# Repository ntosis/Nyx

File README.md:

# Nyx
Nyx Project is a FOC algorith for PMSM Motors based on ARM STM32F446RE, DRV8304 and Simulink. 

The Project NYX is under development and the application software has been developed with Simulink. 
The PCB is not ready and based on DRV8304 fromm Texas Instruments. 
The first tries has been made on EVAL Board from Texas Instruments 'boostxl-drv8304h'

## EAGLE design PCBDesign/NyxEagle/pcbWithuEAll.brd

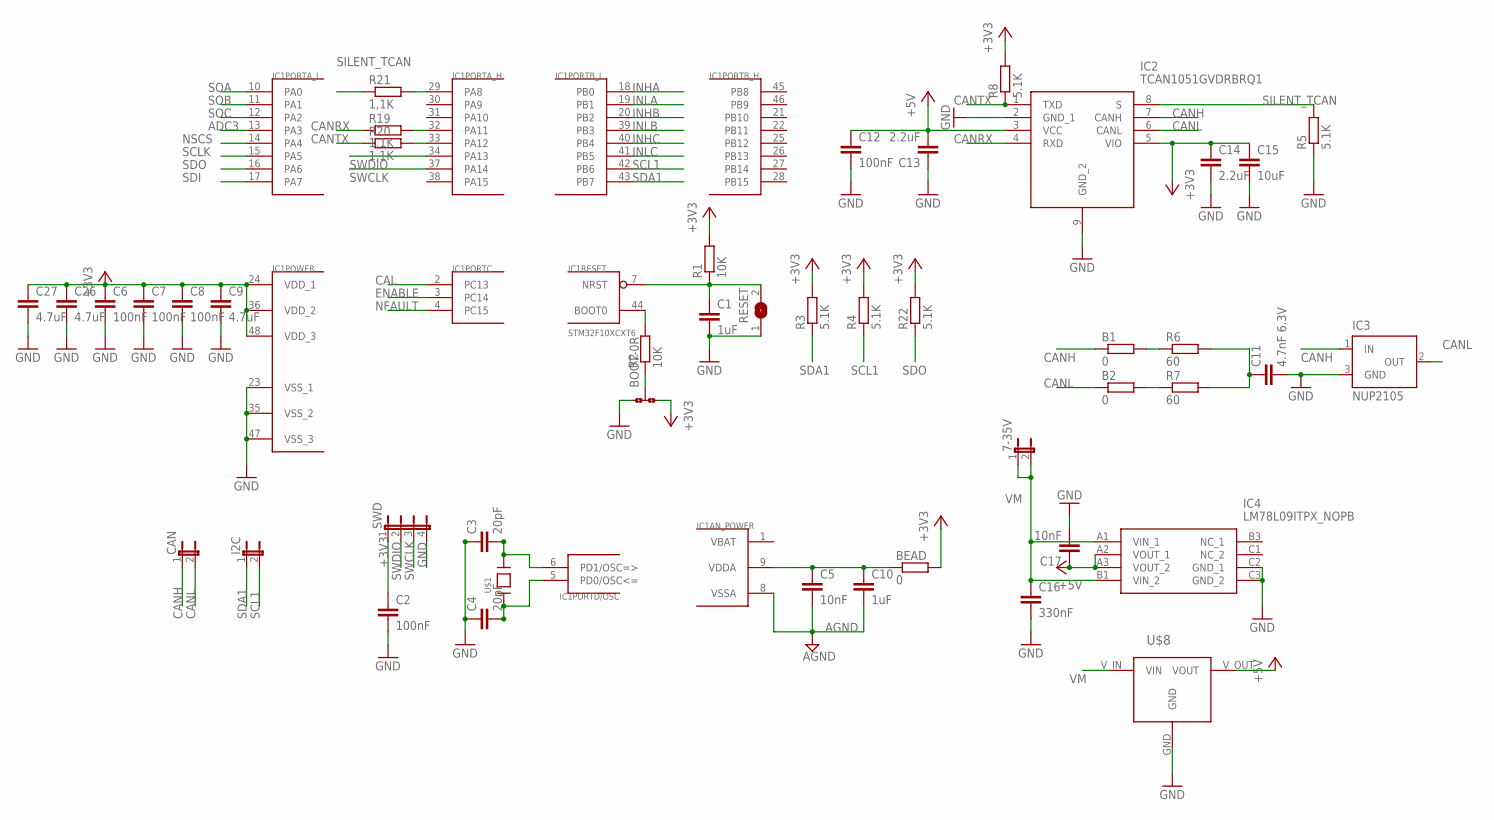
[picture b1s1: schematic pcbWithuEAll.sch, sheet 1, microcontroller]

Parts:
7-35V: JP1E; JP1
B1, B2: 0; R0805
BEAD: 0; R0805
BOOT: 0R-JUMPB; B0R-JMP
C1: 1uF; C0603
C2, C6, C7, C8, C12: 100nF; C0603
C3, C4: 20pF; C0603
C5, C17: 10nF; C0603
C9, C26, C27: 4.7uF; C0603
C10: 1uF; C0805K
C11: 4.7nF 6.3V; C0603
C13, C14: 2.2uF; C0603
C15: 10uF; C0603
C16: 330nF; C0603
CAN: JP1E; JP1
I2C: JP1E; JP1
IC1: STM32F10XCXT6; TQFP48
IC2: TCAN1051GVDRBRQ1; DRB-8
IC3: NUP2105; SOT23
IC4: LM78L09ITPX_NOPB; BGA8C50P3X3_131X131X58
R1, R2: 10K; R0603
R3, R4, R8, R22: 5.1K; R0603
R5: 5.1K; R0402
R6, R7: 60; R0603
R19, R20, R21: 1,1K; R0603
RESET: SJ
SWD: JP4E; JP4
U$1: QUARZ8MHZ; SMD5*3.2MM
U$8: MCP1799T-3302H; SOT23

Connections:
+3V3: BEAD.2, BOOT.3, C2.1, C6.1, C7.1, C8.1, C9.1, C14.1, C15.1, C26.1, C27.1, IC1.24 (VDD_1), IC1.36 (VDD_2), IC1.48 (VDD_3), IC2.5 (VIO), R1.2, R3.2, R4.2, R8.2, R22.2, SWD.1; also elsewhere on the board
+5V: C12.1, C13.2, C17.1, IC2.3 (VCC), IC4.A2 (VOUT_1), IC4.A3 (VOUT_2), U$8.V_OUT (VOUT)
ADC3: IC1.13 (PA3)
AGND: C5.2, C10.2, IC1.8 (VSSA); also elsewhere on the board
CAL: IC1.2 (PC13); also elsewhere on the board
CANH: B1.1, CAN.1, IC2.7 (CANH), IC3.1 (IN)
CANL: B2.1, CAN.2, IC2.6 (CANL), IC3.2 (OUT)
CANRX: IC2.4 (RXD), R19.1
CANTX: IC2.1 (TXD), R8.1, R20.1
ENABLE: IC1.3 (PC14); also elsewhere on the board
GND: BOOT.1, C1.2, C2.2, C3.1, C4.1, C6.2, C7.2, C8.2, C9.2, C11.2, C12.2, C13.1, C14.2, C15.2, C16.2, C17.2, C26.2, C27.2, IC1.23 (VSS_1), IC1.35 (VSS_2), IC1.47 (VSS_3), IC2.2 (GND_1), IC2.9 (GND_2), IC3.3 (GND), IC4.C2 (GND_1), IC4.C3 (GND_2), R5.1, RESET.1, SWD.4, U$8.GND; also elsewhere on the board
INHA: IC1.18 (PB0); also elsewhere on the board
INHB: IC1.20 (PB2); also elsewhere on the board
INHC: IC1.40 (PB4); also elsewhere on the board
INLA: IC1.19 (PB1); also elsewhere on the board
INLB: IC1.39 (PB3); also elsewhere on the board
INLC: IC1.41 (PB5); also elsewhere on the board
unnamed: C1.1, IC1.7 (NRST), R1.1, RESET.2
unnamed: C3.2, IC1.6 (PD1/OSC=>), U$1.P$2
unnamed: C4.2, IC1.5 (PD0/OSC<=), U$1.P$1
unnamed: IC1.44 (BOOT0), R2.2
unnamed: BEAD.1, C5.1, C10.1, IC1.9 (VDDA)
unnamed: BOOT.2, R2.1
unnamed: C11.1, R6.2, R7.2
unnamed: B1.2, R6.1
unnamed: B2.2, R7.1
unnamed: IC1.32 (PA11), R19.2
unnamed: IC1.33 (PA12), R20.2
unnamed: IC1.29 (PA8), R21.2
NFAULT: IC1.4 (PC15); also elsewhere on the board
NSCS: IC1.14 (PA4); also elsewhere on the board
SCL1: I2C.2, IC1.42 (PB6), R4.1
SCLK: IC1.15 (PA5); also elsewhere on the board
SDA1: I2C.1, IC1.43 (PB7), R3.1
SDI: IC1.17 (PA7); also elsewhere on the board
SDO: IC1.16 (PA6), R22.1; also elsewhere on the board
SILENT_TCAN: IC2.8 (S), R5.2, R21.1
SOA: IC1.10 (PA0); also elsewhere on the board
SOB: IC1.11 (PA1); also elsewhere on the board
SOC: IC1.12 (PA2); also elsewhere on the board
SWCLK: IC1.37 (PA14), SWD.3
SWDIO: IC1.34 (PA13), SWD.2
VBAT: IC1.1 (VBAT)
VM: 7-35V.1, 7-35V.2, C16.1, IC4.A1 (VIN_1), IC4.B1 (VIN_2), U$8.V_IN (VIN); also elsewhere on the board

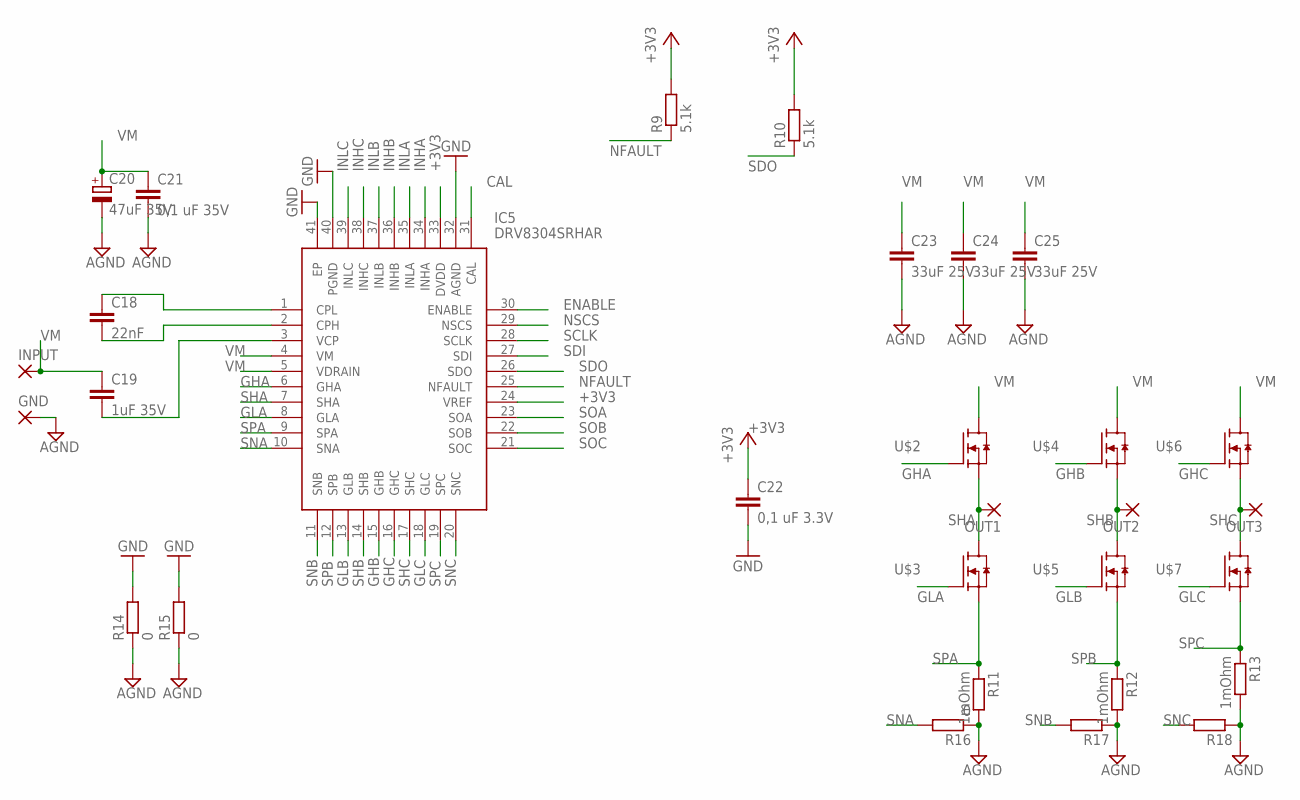
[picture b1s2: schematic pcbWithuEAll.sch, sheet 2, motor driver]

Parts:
C18: 22nF; C0805K
C19: 1uF 35V; C0805K
C20: 47uF 35V; E7,5-16
C21: 0,1 uF 35V; C0805K
C22: 0,1 uF 3.3V; C0805K
C23, C24, C25: 33uF 25V; C1206K
GND: 3,17/1,3
IC5: DRV8304SRHAR; QFN50P600X600X100-41N
INPUT: 3,17/1,3
OUT1, OUT2, OUT3: SMD2; SMD1,27-2,54
R9, R10: 5.1k; R0603
R11, R12, R13: 1mOhm; 1216
R14, R15: 0; R0805W
R16: 0; R0201
R17, R18: R-EU_R0201; R0201
U$2, U$3, U$4, U$5, U$6, U$7: SIRA80DP-T1-RE3-CLASSIC; SI7852ADPT1GE3

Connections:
+3V3: C22.1, IC5.24 (VREF), IC5.33 (DVDD), R9.2, R10.2; also elsewhere on the board
AGND: C20.-, C21.2, C23.2, C24.2, C25.2, GND.1, R11.P$2 (2), R11.P$4 (2), R12.P$2 (2), R12.P$4 (2), R13.P$2 (2), R13.P$4 (2), R14.1, R15.1, R16.1, R17.1, R18.1; also elsewhere on the board
CAL: IC5.31 (CAL); also elsewhere on the board
ENABLE: IC5.30 (ENABLE); also elsewhere on the board
GHA: IC5.6 (GHA), U$2.4 (G)
GHB: IC5.15 (GHB), U$4.4 (G)
GHC: IC5.16 (GHC), U$6.4 (G)
GLA: IC5.8 (GLA), U$3.4 (G)
GLB: IC5.13 (GLB), U$5.4 (G)
GLC: IC5.18 (GLC), U$7.4 (G)
GND: C22.2, IC5.32 (AGND), IC5.40 (PGND), IC5.41 (EP), R14.2, R15.2; also elsewhere on the board
INHA: IC5.34 (INHA); also elsewhere on the board
INHB: IC5.36 (INHB); also elsewhere on the board
INHC: IC5.38 (INHC); also elsewhere on the board
INLA: IC5.35 (INLA); also elsewhere on the board
INLB: IC5.37 (INLB); also elsewhere on the board
INLC: IC5.39 (INLC); also elsewhere on the board
unnamed: C18.1, IC5.1 (CPL)
unnamed: C18.2, IC5.2 (CPH)
unnamed: C19.2, IC5.3 (VCP)
NFAULT: IC5.25 (NFAULT), R9.1; also elsewhere on the board
NSCS: IC5.29 (NSCS); also elsewhere on the board
SCLK: IC5.28 (SCLK); also elsewhere on the board
SDI: IC5.27 (SDI); also elsewhere on the board
SDO: IC5.26 (SDO), R10.1; also elsewhere on the board
SHA: IC5.7 (SHA), OUT1.1, U$2.1 (S), U$2.2 (S), U$2.3 (S), U$3.5 (D), U$3.6 (D), U$3.7 (D), U$3.8 (D), U$3.9 (D), U$3.10 (D), U$3.11 (D)
SHB: IC5.14 (SHB), OUT2.1, U$4.1 (S), U$4.2 (S), U$4.3 (S), U$5.5 (D), U$5.6 (D), U$5.7 (D), U$5.8 (D), U$5.9 (D), U$5.10 (D), U$5.11 (D)
SHC: IC5.17 (SHC), OUT3.1, U$6.1 (S), U$6.2 (S), U$6.3 (S), U$7.5 (D), U$7.6 (D), U$7.7 (D), U$7.8 (D), U$7.9 (D), U$7.10 (D), U$7.11 (D)
SNA: IC5.10 (SNA), R16.2
SNB: IC5.11 (SNB), R17.2
SNC: IC5.20 (SNC), R18.2
SOA: IC5.23 (SOA); also elsewhere on the board
SOB: IC5.22 (SOB); also elsewhere on the board
SOC: IC5.21 (SOC); also elsewhere on the board
SPA: IC5.9 (SPA), R11.P$1 (1), R11.P$3 (1), U$3.1 (S), U$3.2 (S), U$3.3 (S)
SPB: IC5.12 (SPB), R12.P$1 (1), R12.P$3 (1), U$5.1 (S), U$5.2 (S), U$5.3 (S)
SPC: IC5.19 (SPC), R13.P$1 (1), R13.P$3 (1), U$7.1 (S), U$7.2 (S), U$7.3 (S)
VM: C19.1, C20.+, C21.1, C23.1, C24.1, C25.1, IC5.4 (VM), IC5.5 (VDRAIN), INPUT.1, U$2.5 (D), U$2.6 (D), U$2.7 (D), U$2.8 (D), U$2.9 (D), U$2.10 (D), U$2.11 (D), U$4.5 (D), U$4.6 (D), U$4.7 (D), U$4.8 (D), U$4.9 (D), U$4.10 (D), U$4.11 (D), U$6.5 (D), U$6.6 (D), U$6.7 (D), U$6.8 (D), U$6.9 (D), U$6.10 (D), U$6.11 (D); also elsewhere on the board

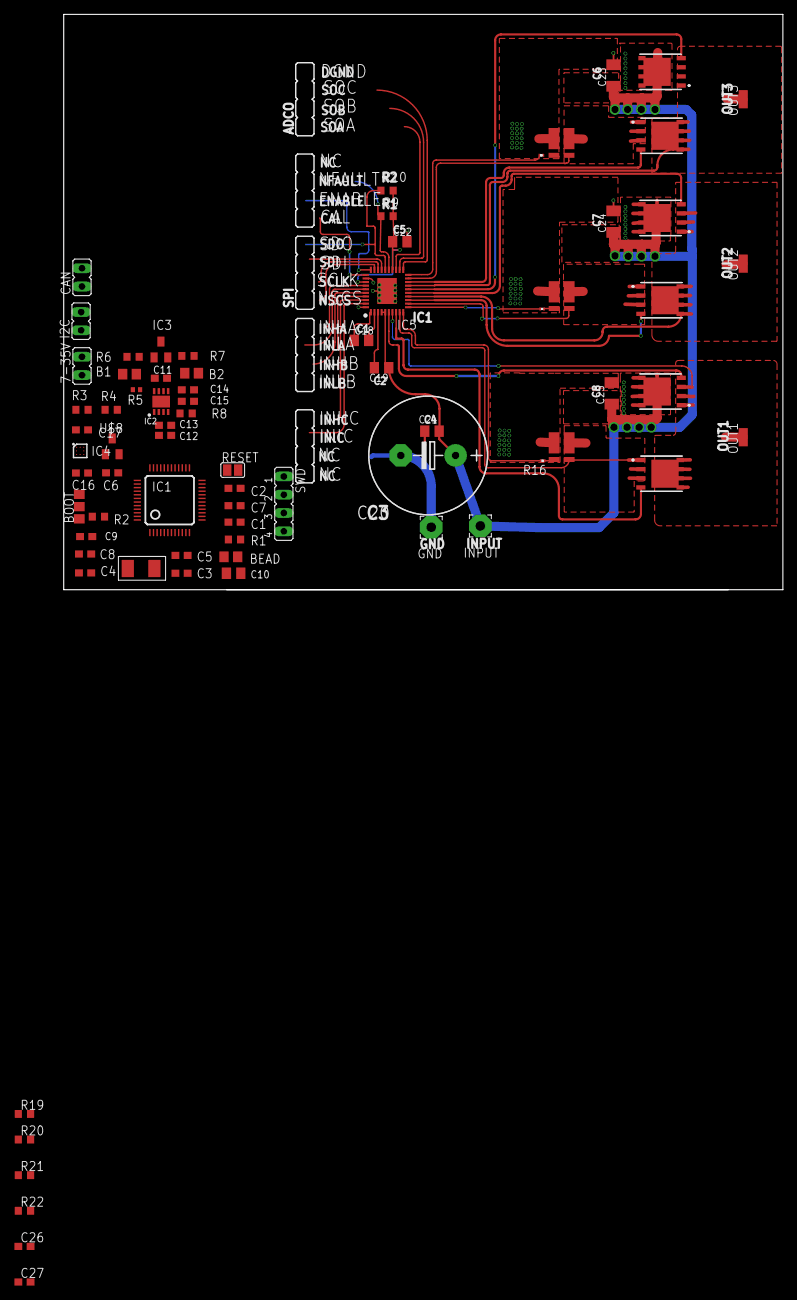
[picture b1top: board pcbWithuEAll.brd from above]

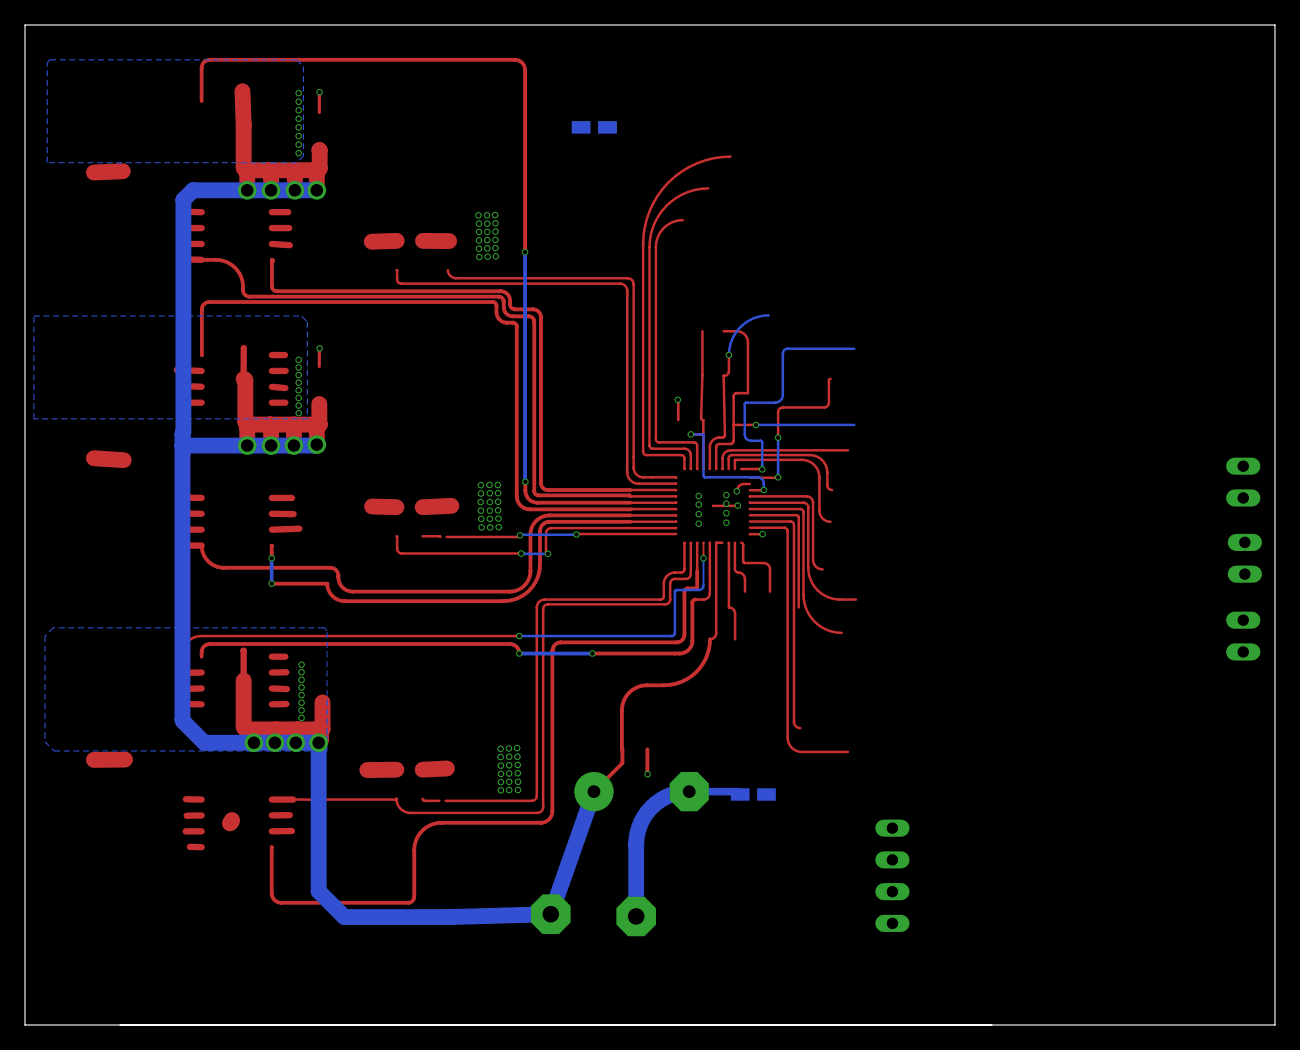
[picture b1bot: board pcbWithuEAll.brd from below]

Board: 2 copper layers, 100.0 x 80.0 mm, 76 parts (2 on the bottom side), 60 nets.

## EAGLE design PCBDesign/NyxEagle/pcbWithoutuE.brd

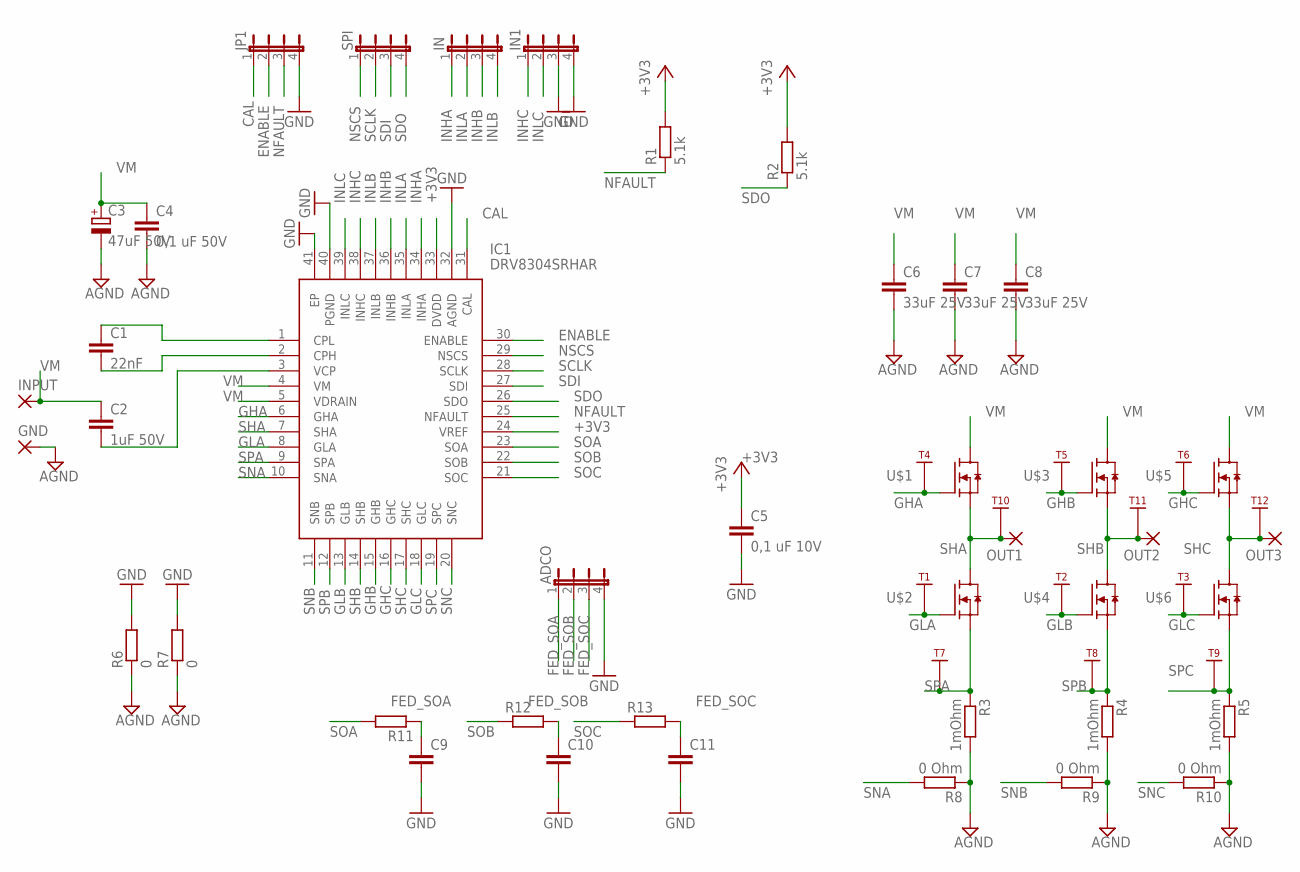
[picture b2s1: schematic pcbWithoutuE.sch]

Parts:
ADCO: JP4E; JP4
C1: 22nF; C0805K
C2: 1uF 50V; C0805K
C3: 47uF 50V; E7,5-16
C4: 0,1 uF 50V; C0805K
C5: 0,1 uF 10V; C0805K
C6, C7, C8: 33uF 25V; C1206K
C9, C10, C11: C-EUC0805; C0805
GND: 3,17/1,3
IC1: DRV8304SRHAR; QFN50P600X600X100-41N
IN, IN1: JP4E; JP4
INPUT: 3,17/1,3
JP1: JP4E; JP4
OUT1, OUT2, OUT3: SMD2; SMD1,27-2,54
R1, R2: 5.1k; R0805
R3, R4, R5: 1mOhm; 1216
R6, R7: 0; R0805W
R8, R9, R10: 0 Ohm; R0603
R11, R12, R13: R-EU_R0805; R0805
SPI: JP4E; JP4
T1, T2, T3, T4, T5, T6, T7, T8, T9, T10, T11, T12: TEST_POINT1593; TURRET_TERMINAL_1593
U$1, U$2, U$3, U$4, U$5, U$6: SIRA80DP-T1-RE3-CLASSIC; SI7852ADPT1GE3

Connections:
+3V3: C5.1, IC1.24 (VREF), IC1.33 (DVDD), R1.2, R2.2
AGND: C3.-, C4.2, C6.2, C7.2, C8.2, GND.1, R3.P$2 (2), R3.P$4 (2), R4.P$2 (2), R4.P$4 (2), R5.P$2 (2), R5.P$4 (2), R6.1, R7.1, R8.1, R9.1, R10.1
CAL: IC1.31 (CAL), JP1.1
ENABLE: IC1.30 (ENABLE), JP1.2
FED_SOA: ADCO.1, C9.1, R11.1
FED_SOB: ADCO.2, C10.1, R12.2
FED_SOC: ADCO.3, C11.1, R13.2
GHA: IC1.6 (GHA), T4.1, U$1.4 (G)
GHB: IC1.15 (GHB), T5.1, U$3.4 (G)
GHC: IC1.16 (GHC), T6.1, U$5.4 (G)
GLA: IC1.8 (GLA), T1.1, U$2.4 (G)
GLB: IC1.13 (GLB), T2.1, U$4.4 (G)
GLC: IC1.18 (GLC), T3.1, U$6.4 (G)
GND: ADCO.4, C5.2, C9.2, C10.2, C11.2, IC1.32 (AGND), IC1.40 (PGND), IC1.41 (EP), IN1.3, IN1.4, JP1.4, R6.2, R7.2
INHA: IC1.34 (INHA), IN.1
INHB: IC1.36 (INHB), IN.3
INHC: IC1.38 (INHC), IN1.1
INLA: IC1.35 (INLA), IN.2
INLB: IC1.37 (INLB), IN.4
INLC: IC1.39 (INLC), IN1.2
unnamed: C1.1, IC1.1 (CPL)
unnamed: C1.2, IC1.2 (CPH)
unnamed: C2.2, IC1.3 (VCP)
NFAULT: IC1.25 (NFAULT), JP1.3, R1.1
NSCS: IC1.29 (NSCS), SPI.1
SCLK: IC1.28 (SCLK), SPI.2
SDI: IC1.27 (SDI), SPI.3
SDO: IC1.26 (SDO), R2.1, SPI.4
SHA: IC1.7 (SHA), OUT1.1, T10.1, U$1.1 (S), U$1.2 (S), U$1.3 (S), U$2.5 (D), U$2.6 (D), U$2.7 (D), U$2.8 (D), U$2.9 (D), U$2.10 (D), U$2.11 (D)
SHB: IC1.14 (SHB), OUT2.1, T11.1, U$3.1 (S), U$3.2 (S), U$3.3 (S), U$4.5 (D), U$4.6 (D), U$4.7 (D), U$4.8 (D), U$4.9 (D), U$4.10 (D), U$4.11 (D)
SHC: IC1.17 (SHC), OUT3.1, T12.1, U$5.1 (S), U$5.2 (S), U$5.3 (S), U$6.5 (D), U$6.6 (D), U$6.7 (D), U$6.8 (D), U$6.9 (D), U$6.10 (D), U$6.11 (D)
SNA: IC1.10 (SNA), R8.2
SNB: IC1.11 (SNB), R9.2
SNC: IC1.20 (SNC), R10.2
SOA: IC1.23 (SOA), R11.2
SOB: IC1.22 (SOB), R12.1
SOC: IC1.21 (SOC), R13.1
SPA: IC1.9 (SPA), R3.P$1 (1), R3.P$3 (1), T7.1, U$2.1 (S), U$2.2 (S), U$2.3 (S)
SPB: IC1.12 (SPB), R4.P$1 (1), R4.P$3 (1), T8.1, U$4.1 (S), U$4.2 (S), U$4.3 (S)
SPC: IC1.19 (SPC), R5.P$1 (1), R5.P$3 (1), T9.1, U$6.1 (S), U$6.2 (S), U$6.3 (S)
VM: C2.1, C3.+, C4.1, C6.1, C7.1, C8.1, IC1.4 (VM), IC1.5 (VDRAIN), INPUT.1, U$1.5 (D), U$1.6 (D), U$1.7 (D), U$1.8 (D), U$1.9 (D), U$1.10 (D), U$1.11 (D), U$3.5 (D), U$3.6 (D), U$3.7 (D), U$3.8 (D), U$3.9 (D), U$3.10 (D), U$3.11 (D), U$5.5 (D), U$5.6 (D), U$5.7 (D), U$5.8 (D), U$5.9 (D), U$5.10 (D), U$5.11 (D)

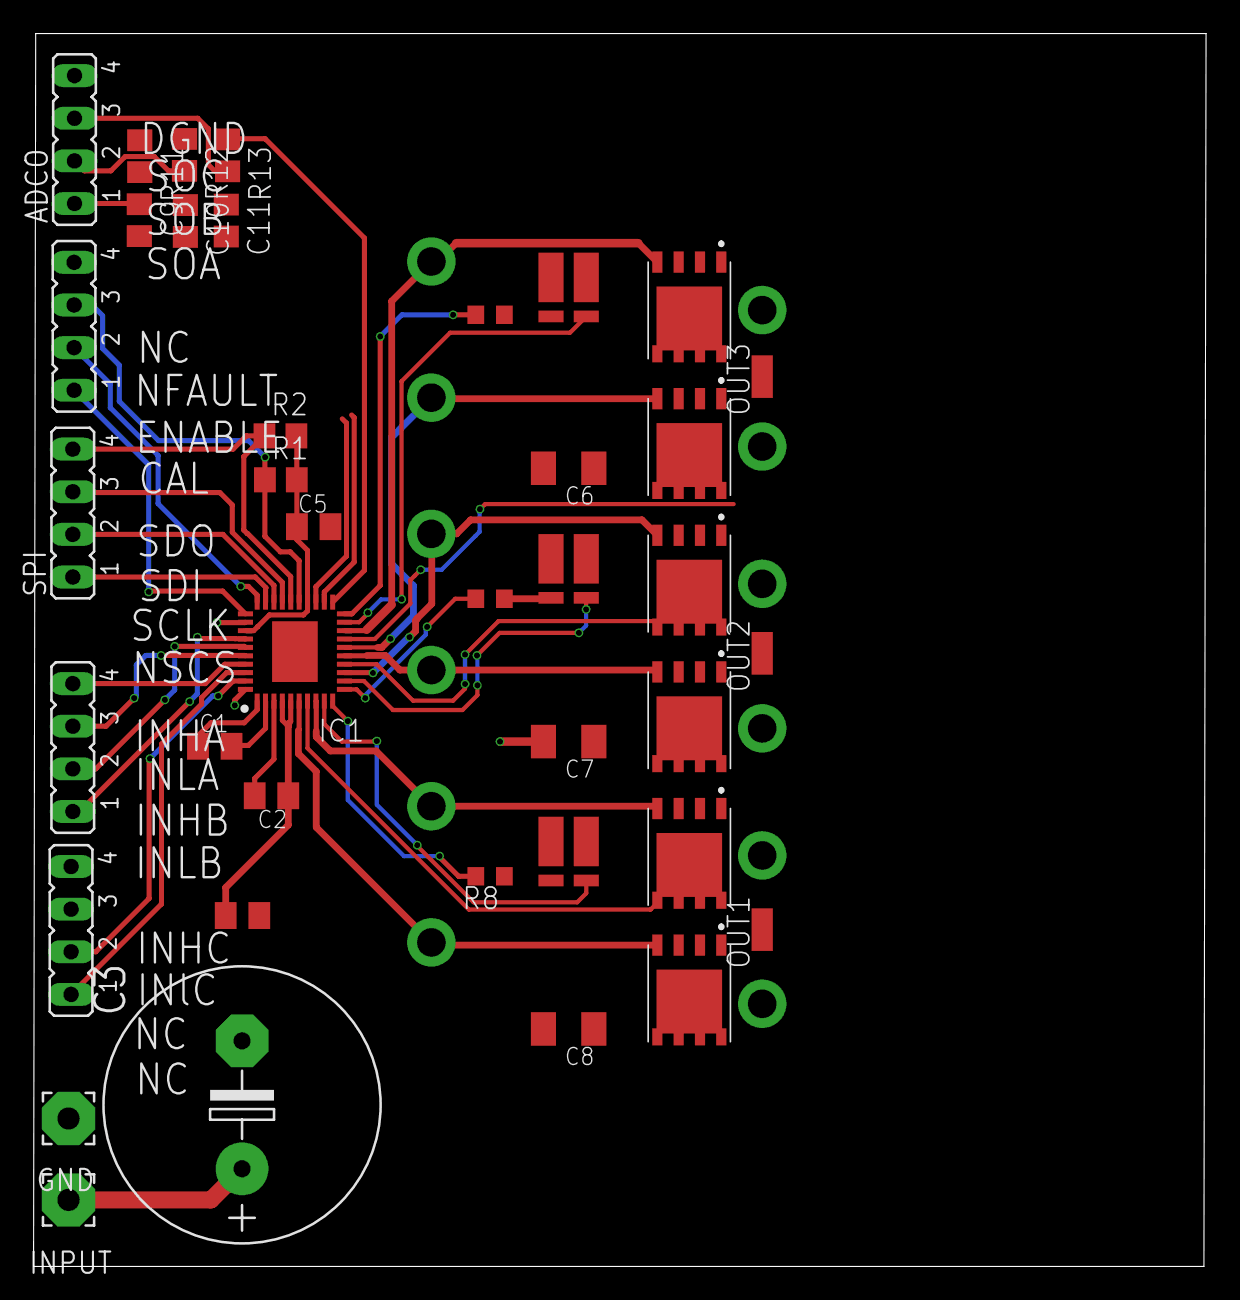
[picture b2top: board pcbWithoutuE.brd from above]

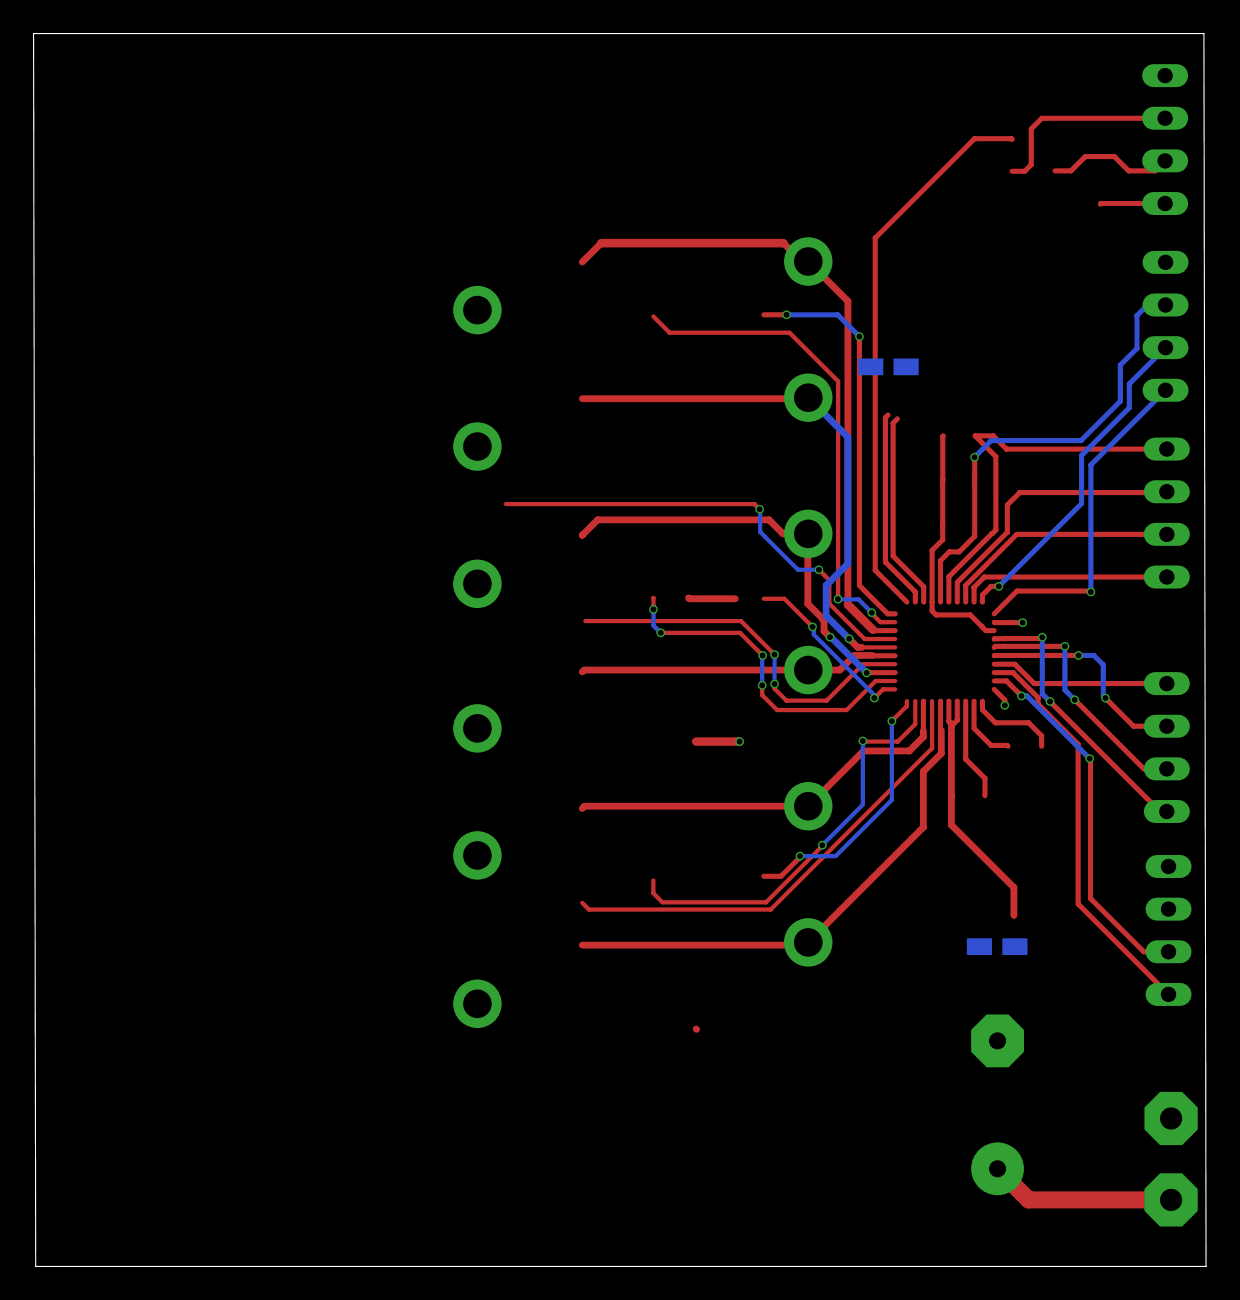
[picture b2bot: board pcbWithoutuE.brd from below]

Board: 2 copper layers, 69.9 x 73.4 mm, 53 parts (2 on the bottom side), 41 nets.

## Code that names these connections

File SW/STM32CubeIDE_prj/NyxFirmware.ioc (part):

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Mcu.Name=STM32F103C(8-B)Tx
Mcu.Package=LQFP48
Mcu.UserName=STM32F103C8Tx
PA1.GPIOParameters=GPIO_Label
PA1.GPIO_Label=SOA_AI
PA1.Signal=ADCx_IN1
PA10.GPIOParameters=GPIO_Label
PA10.GPIO_Label=DRV_NFAULT
PA10.Signal=GPIO_Input
PA13.Mode=Serial_Wire
PA13.Signal=SYS_JTMS-SWDIO
PA14.Mode=Serial_Wire
PA14.Signal=SYS_JTCK-SWCLK
PA15.GPIOParameters=GPIO_Label
PA15.GPIO_Label=PWM_INHA
PA15.Signal=S_TIM2_CH1_ETR
PA2.GPIOParameters=GPIO_Label
PA2.GPIO_Label=SOB_AI
PA2.Signal=ADCx_IN2
PA4.GPIOParameters=GPIO_Speed,PinState,GPIO_Label
PA4.GPIO_Label=DRV_CS
PA4.GPIO_Speed=GPIO_SPEED_FREQ_HIGH
PA4.PinState=GPIO_PIN_SET
PA4.Signal=GPIO_Output
PA5.Mode=Full_Duplex_Master
PA5.Signal=SPI1_SCK
PA6.Mode=Full_Duplex_Master
PA6.Signal=SPI1_MISO
PA7.Mode=Full_Duplex_Master
PA7.Signal=SPI1_MOSI
PA9.GPIOParameters=GPIO_Label
PA9.GPIO_Label=DRV_ENABLE
PA9.Signal=GPIO_Output
PB0.GPIOParameters=GPIO_Label
PB0.GPIO_Label=DRV_INLB
PB0.Signal=GPIO_Output
PB1.GPIOParameters=GPIO_Label
PB1.GPIO_Label=DRV_INLA
PB1.Signal=GPIO_Output
PB3.GPIOParameters=GPIO_Label
PB3.GPIO_Label=PWM_INHB
PB3.Signal=S_TIM2_CH2
PB5.GPIOParameters=GPIO_Label
PB5.GPIO_Label=DRV_INLC
PB5.Signal=GPIO_Output
PB9.GPIOParameters=GPIO_Label
PB9.GPIO_Label=PWM_INHC
PB9.Signal=S_TIM4_CH4
PC13-TAMPER-RTC.GPIOParameters=GPIO_Speed,GPIO_PuPd
PC13-TAMPER-RTC.GPIO_PuPd=GPIO_PULLDOWN
PC13-TAMPER-RTC.GPIO_Speed=GPIO_SPEED_FREQ_MEDIUM
PC13-TAMPER-RTC.Signal=GPIO_Output
PC14-OSC32_IN.GPIOParameters=GPIO_Speed,GPIO_PuPd
PC14-OSC32_IN.GPIO_PuPd=GPIO_PULLDOWN
PC14-OSC32_IN.GPIO_Speed=GPIO_SPEED_FREQ_MEDIUM
PC14-OSC32_IN.Signal=GPIO_Output
PC15-OSC32_OUT.GPIOParameters=GPIO_Speed,GPIO_PuPd
PC15-OSC32_OUT.GPIO_PuPd=GPIO_PULLDOWN
PC15-OSC32_OUT.GPIO_Speed=GPIO_SPEED_FREQ_MEDIUM
PC15-OSC32_OUT.Signal=GPIO_Output
PD0-OSC_IN.Mode=HSE-External-Oscillator
PD0-OSC_IN.Signal=RCC_OSC_IN
PD1-OSC_OUT.Mode=HSE-External-Oscillator
PD1-OSC_OUT.Signal=RCC_OSC_OUT
RCC.SYSCLKFreq_VALUE=64000000
RCC.SYSCLKSource=RCC_SYSCLKSOURCE_PLLCLK
board=custom

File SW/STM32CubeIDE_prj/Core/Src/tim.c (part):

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
    __HAL_RCC_GPIOA_CLK_ENABLE();
    /**TIM5 GPIO Configuration
    PA0-WKUP     ------> TIM5_CH1
    PA1     ------> TIM5_CH2
    */
    GPIO_InitStruct.Pin = Sensor_in1_Pin|Sensor_in2_Pin;
    GPIO_InitStruct.Mode = GPIO_MODE_AF_PP;
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  /* USER CODE END TIM1_MspPostInit 0 */
    __HAL_RCC_GPIOA_CLK_ENABLE();
    /**TIM1 GPIO Configuration
    PA8     ------> TIM1_CH1
    PA10     ------> TIM1_CH3
    */
    GPIO_InitStruct.Pin = GPIO_PIN_8|GPIO_PIN_10;
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
    __HAL_RCC_GPIOB_CLK_ENABLE();
    /**TIM4 GPIO Configuration
    PB6     ------> TIM4_CH1
    */
    GPIO_InitStruct.Pin = PWM_INHC_Pin;
    GPIO_InitStruct.Mode = GPIO_MODE_AF_PP;
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    __HAL_RCC_TIM5_CLK_DISABLE();

    /**TIM5 GPIO Configuration
    PA0-WKUP     ------> TIM5_CH1
    PA1     ------> TIM5_CH2
    */
    HAL_GPIO_DeInit(GPIOA, Sensor_in1_Pin|Sensor_in2_Pin);

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
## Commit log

2020-02-08 Change of shunt resistors to smaller.
2020-02-15 PCB is ready and before the silk layer.
2020-02-15 Silk layer is ready
2020-02-28 added forgoten polygon for VM signal in a mosfet.
2020-03-16 New IDE Project created and schematic with uE is updated.
2020-03-19 Big in FreeRTOS changed to heap3. Configured ADC with DMA. A task is triggered every 100 us.
2020-04-30 Added the DRV8304 component, which is used to configure the IC motor driver with the same name.
2020-05-02 Changed SPI Clock Edge setting to rising edge. Added Read Register function for drv8304 and added a function to read via SPI after reset of the controller, if the chip is locked.
2020-06-14 Added PWM Signal, fixed SPI Issue during to lock DRV8304 and added two debug derectives for the scheduller.
2020-06-28 Change PWM Freq to 10Khz, Change PWM Channel to CH4. Lower SPI Freq, Rearange GPIO Pins. ADC is modified to be triggered from PWM and use the DMA to copy the result to an array. Fix in DRV8304 Init C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
2020-06-28 This commit can turn the motor but in very bad manner.
2021-01-06 Update 2MsqBWlHyHIOe1URRudn9vMM7Uod.xml, j4xwF_j8iFTVayUMfxLgMnTbencd.xml, and 58 more files...
2021-01-06 added Matlab code
2021-01-14 ADC is configured to trigert on PWM rise edge. Ingected and regular ADC groups are activated. For PWM signal now are three channels configured.
2021-01-30 Uncalibrated software which C code is working.
2021-01-30 forgoten file.
2021-02-03 CPU Clocks for Step Function enviroment. C13-C14 Pins are used to measure cpu clocks.
2021-02-27 Hooray, motor is spinning with constant speed. Change the Hardware to TI Eval board and adapted the shunt resistor value.
2021-03-11 added direkt lookup table for the ADC to Voltage. But bug with overflow dt exist in this version.
2021-10-20 Model alligment with the generated C code.
2021-10-20 Position observer as model reference.
2021-12-20 Update mul_s32_hiSR.h, queue.c, and 59 more files...
2022-01-27 Added new model for safety checks and add auto-calibration variable from ADC.
2022-02-06 Update ComputationINTfunc.ais, ComputationINTfunc.gdl, and 6 more files...
2022-02-12 new license text
2022-02-12 Change controller to STM32F446RE with FPU.
2022-02-12 Added Simulink Models.
2022-02-12 Add autogenerated make files.
2022-02-13 Update .gitignore in hardware design
2022-02-13 Add pdf documents like datasheet etc.
2022-02-13 Remove reduntant comments and variables.
2022-02-13 Add CalcSpinSpeednDir module.
2022-02-14 Add CI configuration file.
2022-02-14 Update ci.yml
    Fix working directory path for CI
2022-02-14 Update ci.yml
    Change CI trigger to correct brunch name 'master'
2022-02-14 Update project makefile
2022-02-14 Update path for linker script.
2022-02-14 Update ci.yml
    CI update artifact path.
2022-03-05 Remove simulink models from main project
2022-03-05 Adapt library path to correct one.
2022-03-05 Update ci.yml
    Add CI command for submodules.
2022-03-05 Update ci.yml
    fix syntax error
2022-03-06 Update NyxF446RE.launch, .cproject, and 2 more files...
2022-03-06 New Lib and new debug options.
2022-03-06 New simulink lib from 3Marz.
2022-03-09 Change Compile cfg.
2022-03-09 Update to new lib.
2022-03-13 Update InterfaceBswApp.c
    Add debounce counter variable in error reaction function.
2022-03-13 Add more debounce time for the tuning.
2022-03-13 Update lib from submodule.
2022-03-14 Update Nyx_Simulink Lib.
2022-03-14 Update Nyx_Simulink library.
2022-03-20 change name of the main step function.
2022-03-20 Update ci.yml and Nyx_Simulink
2022-03-22 Update Nyx_Simulink to newest lib.
2022-03-23 Update Nyx_Simulink lib to 23Marz22
2022-03-23 Update Nyx_Simulink lib 22Marz22 with first try to tune PI.
2022-03-28 Semihosting working stand.
2022-03-29 Add more variables in print file
2022-04-03 We have a problem with the PWM input measurment for the angle sensor.
2022-04-03 Add filter in PWM input mode in hardware and fix the c code to calculate correctly the pwm duty cycle input from the sensor.
2022-04-09 Change PWM Input filter for the timer8 to be bigger.
2022-04-09 Add #ifdef derectives for semihosting and debugging.
2022-04-09 Add Semihosting derective in Main.c and update eclipse project file.
2022-06-22 Add timer 8 counter overflow interrupt to catch PWM = 0%.
2022-06-22 Set bit URS from timer 8 manually, because CubeMX dont support this mode. That mode tells to controller to trigger the update event interrupt only when counter overflows. Rework the PWM in put algori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
2022-10-20 commit all the last changes.
2022-11-13 update all changes
2022-11-20 Changed the timer configuration. Now timer 1 with N Channel is used to drive the PWM Signals. ADC has now the N Channel as Input triger, not internal but external. That means I used a copper bridge t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
2022-11-27 remove dac debug function.
2022-11-27 Remove DAC completly.
2023-07-13 this is a working commit, matlab is incosistent with c code. And the simulink lib is not connected in git, should be connected manually.
2023-07-19 Set task 500ms to run every 10 ms but the name is still the old. Adapt to be compatible with the new interfaces. Remove Semihosting and extend debugig configurations.
2023-07-19 Adapt the interface from simulink to the new name.
2023-07-20 Sync to subproject add in interfaces header a new extern signal from simulink.
2023-07-20 Update ci.yml
    update yaml to use ubuntu 20.04
2023-08-01 some fixes for the scheduller and for the interface.
2023-08-01 connect to new simulink library.

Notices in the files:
SW/STM32CubeIDE_prj/Core/Src/tim.c:
© Copyright (c) 2023 STMicroelectronics.
All rights reserved.
This software component is licensed by ST under Ultimate Liberty license
(C) COPYRIGHT STMicroelectronics *****END OF FILE
